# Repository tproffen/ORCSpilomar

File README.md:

# pi-lomar

## ORCSGirls version

We build this project with one of our students. This is the home for some of the code modifications. 

* Change driver to TMC2209 and control via UART
* New draft PCB to enable UART control of the stepper controllers.

## Based on this project

RaspberryPi based miniature observatory.
A Python3 project to control a small camera and telephoto lens housed in a miniature 3D printed observatory enclosure.
This combines multiple open modules to handle object location, tracking and image capture.

This uses Python3 on the Raspberry Pi and CircuitPython on a connected Pimoroni Tiny2040/Tiny2350 microcontroller.

The physical telescope, mechanism and dome is buildable from the Instructables page.
[https://www.instructables.com/Pi-lomar-3D-Printed-Working-Miniature-Observatory-/]

The wiki for pi-lomar is here.
[https://github.com/Short-bus/pilomar/wiki]

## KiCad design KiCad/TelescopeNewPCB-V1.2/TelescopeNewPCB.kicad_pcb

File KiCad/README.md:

# Circuit Boards

Initial draft *untested* version ot a new PDB allowing UART control of the TMC2209.

The version also includes a connection for a [GPS module](https://learn.adafruit.com/adafruit-ultimate-gps) and a [Temperature and Pressure Sensor](https://learn.adafruit.com/adafruit-am2320-temperature-humidity-i2c-sensor)connected to the I2C bus of the Pi. The board also has two buttons (HOME and STOP) connected to the Pi GPIOs for future use. 

Use at your own risk :)

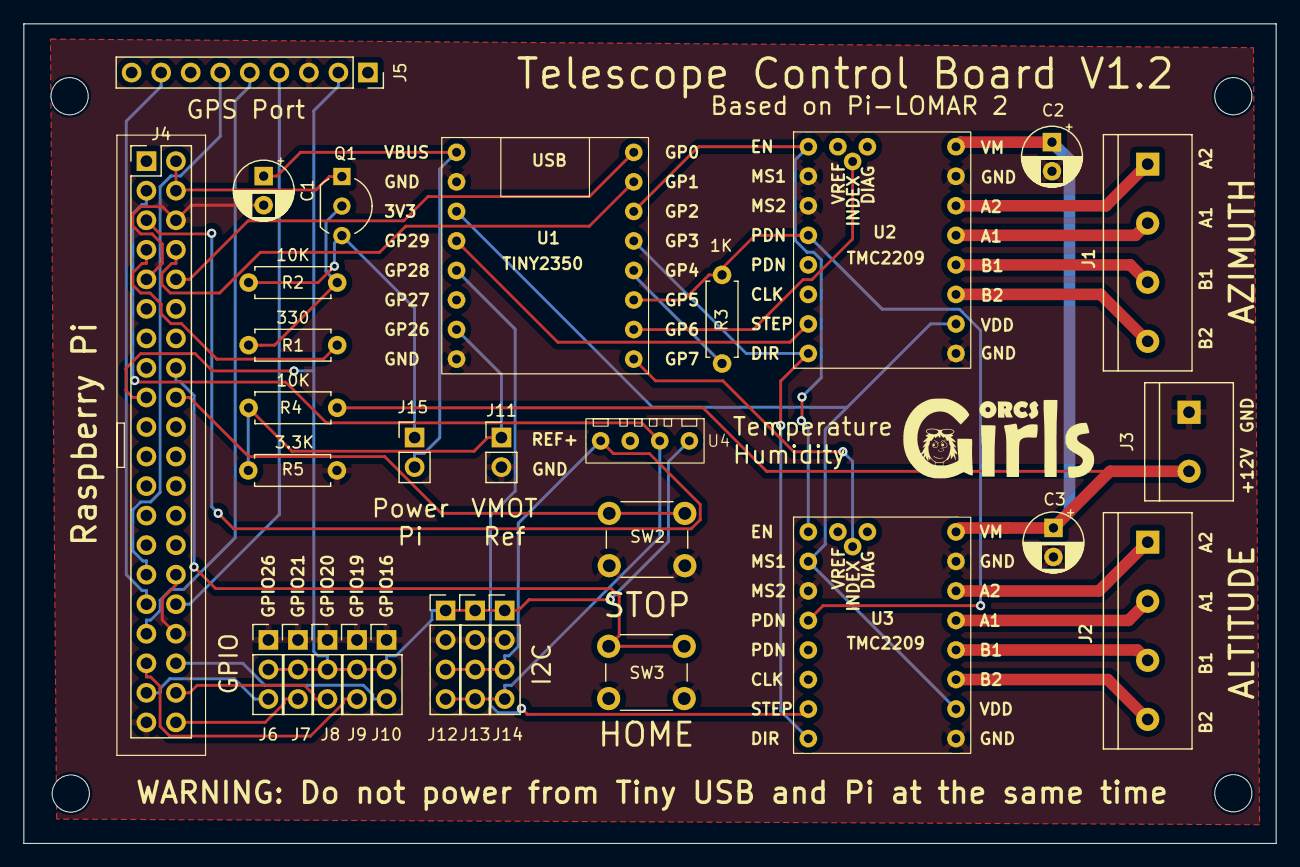
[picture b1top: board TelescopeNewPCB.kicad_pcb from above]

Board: 2 copper layers, 107.7 x 70.5 mm, 35 parts (0 on the bottom side), 41 nets.

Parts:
C1, C2, C3: 47uF; CP_Radial_D5.0mm_P2.50mm
G99: LOGO
H1, H2, H3, H4: MountingHole_3.2mm_M3
J1: Azimuth; TerminalBlock_bornier-4_P5.08mm
J2: Altitude; TerminalBlock_bornier-4_P5.08mm
J3: Power 12V; TerminalBlock_bornier-2_P5.08mm
J4: Pi Connector; PinHeader_2x20_P2.54mm_Vertical
J5: GPS Module; PinSocket_1x09_P2.54mm_Vertical
J6: GPIO26; PinHeader_1x03_P2.54mm_Vertical
J7: GPIO21; PinHeader_1x03_P2.54mm_Vertical
J8: GPI20; PinHeader_1x03_P2.54mm_Vertical
J9: GPI19; PinHeader_1x03_P2.54mm_Vertical
J10: GPI16; PinHeader_1x03_P2.54mm_Vertical
J11: VMOTRef; PinHeader_1x02_P2.54mm_Vertical
J12, J13, J14: I2C; PinHeader_1x04_P2.54mm_Vertical
J15: TinyPower; PinHeader_1x02_P2.54mm_Vertical
Q1: BC548; TO-92_Inline_Wide
R1: 330; R_Axial_DIN0207_L6.3mm_D2.5mm_P7.62mm_Horizontal
R2, R4: 10K; R_Axial_DIN0207_L6.3mm_D2.5mm_P7.62mm_Horizontal
R3: 1K; R_Axial_DIN0207_L6.3mm_D2.5mm_P7.62mm_Horizontal
R5: 3.3K; R_Axial_DIN0207_L6.3mm_D2.5mm_P7.62mm_Horizontal
SW2: HOME; SW_PUSH_6mm_H5mm
SW3: STOP; SW_PUSH_6mm_H5mm
U1: Tiny2350
U2, U3: TMC2209
U4: AM2320

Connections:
3V3: U1.3 (3V3), U2.10 (VCC), U3.2 (MS1), U3.10 (VCC)
5V: J4.2, J4.4, Q1.1 (C)
ALTDIAG: U1.16 (GP7), U3.19 (DIAG)
ALTSTEP: U1.5 (GP28), U3.7 (STEP)
AZMDIAG: U1.15 (GP6), U2.19 (DIAG)
AZMSTEP: U1.4 (GP29), U2.7 (STEP)
DIR: U1.12 (GP3), U2.8 (DIR), U3.8 (DIR)
EN: U1.11 (GP2), U2.1 (EN), U3.1 (EN)
GND: C1.2, C2.2, C3.2, J3.1, J4.6, J4.9, J4.30, J4.34, J4.39, J5.3, J6.1, J7.1, J8.1, J9.1, J10.1, J11.2, J12.2, J13.2, J14.2, R5.2, SW2.2, SW3.2, U1.2 (GND), U1.8 (GND), U2.2 (MS1), U2.3 (MS2), U2.9 (GND), U2.15 (GND), U3.3 (MS2), U3.9 (GND), U3.15 (GND), U4.3 (GND)
GPIO16: J4.36, J10.3
GPIO19: J4.35, J9.3
GPIO20: J4.38, J8.3
GPIO21: J4.40, J7.3
GPIO26: J4.37, J6.3
GPSEN: J4.31, J5.8
GPSFIX: J4.29, J5.6
GPSRX: J4.32, J5.4
GPSTX: J4.33, J5.5
unnamed: J1.1, U2.14 (A2)
unnamed: J1.2, U2.13 (A1)
unnamed: J1.3, U2.12 (B1)
unnamed: J1.4, U2.11 (B2)
unnamed: J2.1, U3.14 (A2)
unnamed: J2.2, U3.13 (A1)
unnamed: J2.3, U3.12 (B1)
unnamed: J2.4, U3.11 (B2)
unnamed: J4.16, SW3.1
unnamed: J4.18, SW2.1
unnamed: J11.1, R4.1, R5.1, U1.7 (GP26)
unnamed: J15.1, Q1.3 (E), R2.2
unnamed: Q1.2 (B), R1.2, R2.1
unnamed: R3.1, U1.13 (GP4)
RX2TX: J4.10, U1.9 (GP0)
SCL: J4.5, J12.3, J13.3, J14.3, U4.4 (SCL)
SDA: J4.3, J12.4, J13.4, J14.4, U4.2 (SDA)
TSWITCH: J4.7, R1.1
TX2RX: J4.8, U1.10 (GP1)
UART: R3.2, U1.14 (GP5), U2.4 (PDN), U3.4 (PDN)
VIN: J4.17, J5.2, J6.2, J7.2, J8.2, J9.2, J10.2, J12.1, J13.1, J14.1, U4.1 (VDD)
VMOT: C2.1, C3.1, J3.2, R4.2, U2.16 (VM), U3.16 (VM)
VTINY: C1.1, J15.2, U1.1 (VBUS)

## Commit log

2024-11-30 Added gps code
2024-11-30 Create install_jupyter
2024-12-01 Initial version for TMC2209
2024-12-01 Line endings fixed and some bugs
2024-12-01 Ongoing
2024-12-01 Ongoing development
2024-12-07 Major rework
2024-12-07 Cleanup
2024-12-08 Woohoo motors move right with new driver :)
2024-12-11 Added PCB
2024-12-11 Updated READMEs
2025-01-19 Small changes to labels
